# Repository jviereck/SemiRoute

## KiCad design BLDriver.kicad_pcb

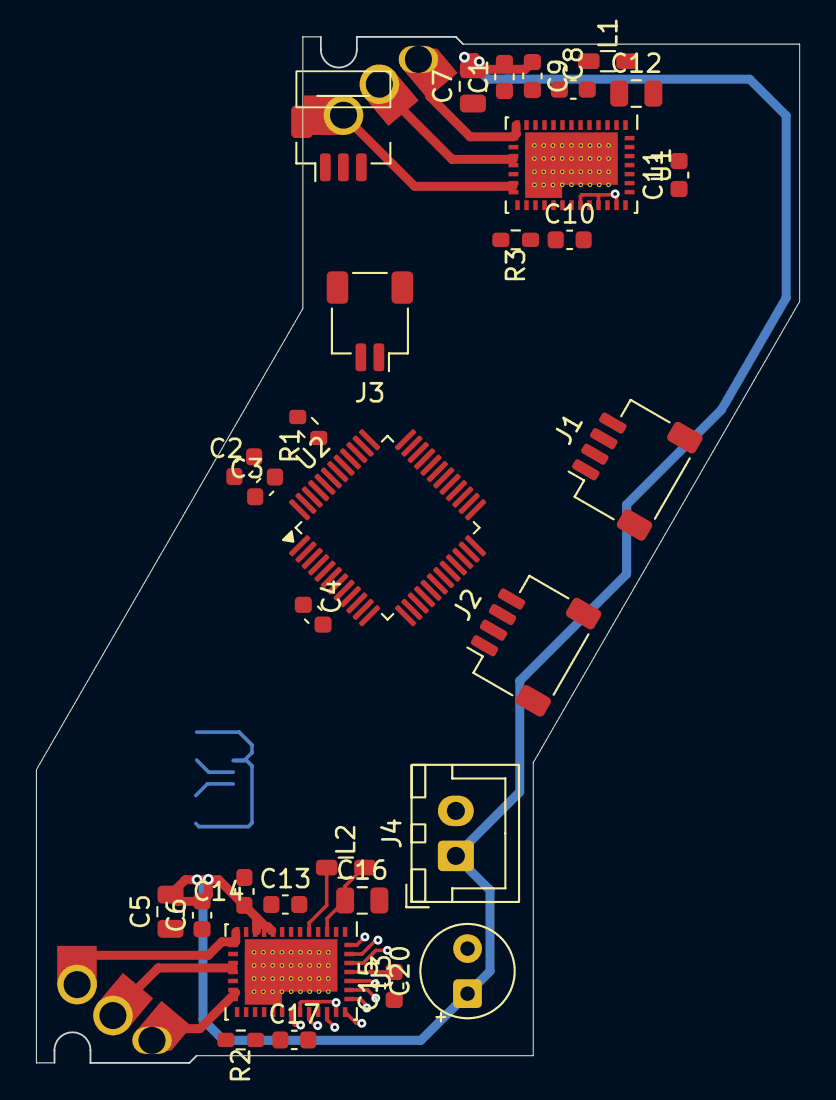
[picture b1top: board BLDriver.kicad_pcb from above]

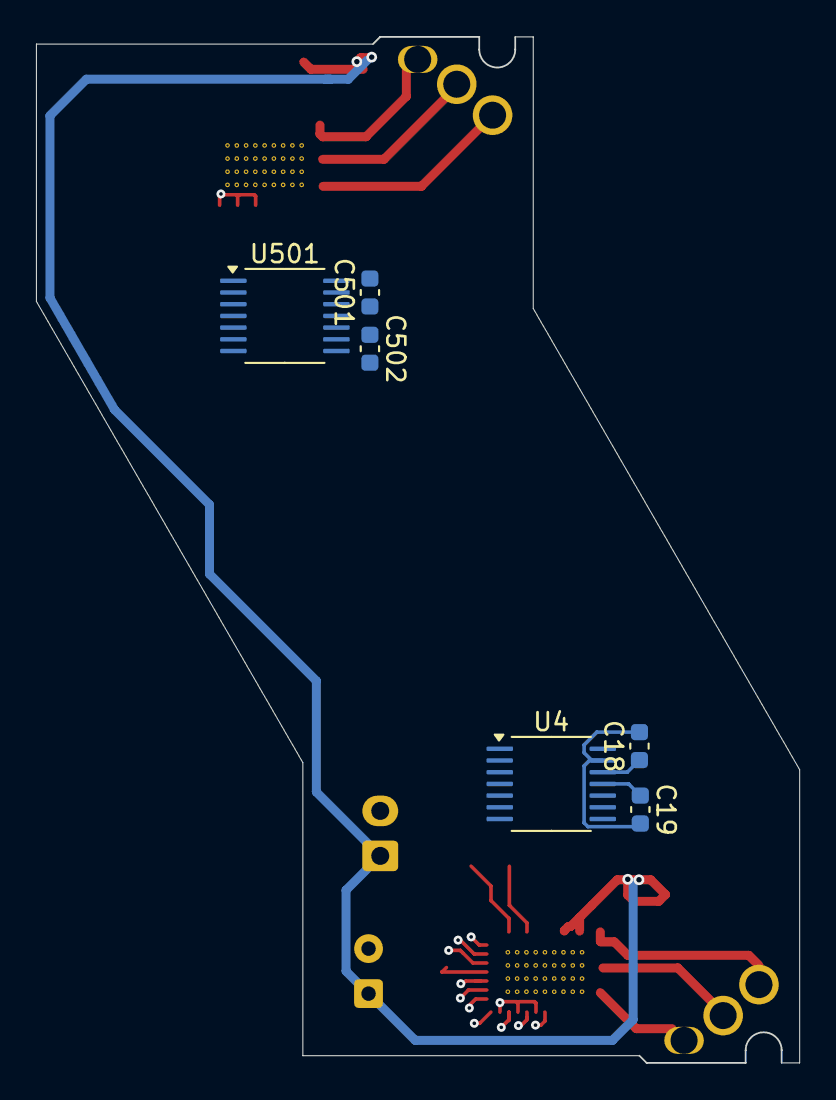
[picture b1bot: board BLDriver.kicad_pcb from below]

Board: 4 copper layers, 42.4 x 57.0 mm, 38 parts (6 on the bottom side), 60 nets.

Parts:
C1, C2, C4, C6, C11, C15: 100nF; C_0603_1608Metric
C3, C9, C10, C14, C17: 1uF; C_0603_1608Metric
C5, C7: 10uF; C_0805_2012Metric
C8, C13: 47nF; C_0603_1608Metric
C12, C16: 22uF; C_0805_2012Metric
C18, C501: 2.2 uF; C_0603_1608Metric
C19, C502: 1 uF; C_0603_1608Metric
C20: 220 uF; CP_Radial_Tantal_D5.0mm_P2.50mm
J1, J2: Conn_01x04_Pin; JST_SH_SM04B-SRSS-TB_1x04-1MP_P1.00mm_Horizontal
J3: Conn_01x02_Pin; JST_SH_SM02B-SRSS-TB_1x02-1MP_P1.00mm_Horizontal
J4: Conn_01x02_Pin; JST_XH_B2B-XH-A_1x02_P2.50mm_Vertical
J5: Conn_01x03_Pin; MotorPogo_A
J6: Conn_01x03_Pin; MotorPogo_B
L1, L2: 47uH; L_0805_2012Metric
R1: 10k; R_0603_1608Metric
R2, R3: 5.1k; R_0603_1608Metric
U1, U3: DRV8316R; QFN-40_EP_5x7_Pitch0.5mm
U2: STM32G071CBT6; LQFP-48_7x7mm_P0.5mm
U4, U501: AS5048A

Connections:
3V3: C2.2, C3.2, C12.1, C18.1, C501.1, L1.2, U1.3 (FB_BK), U2.1 (VDD), U2.9 (VDDA), U2.24 (VDD), U2.48 (VDD), U4.12 (VDD3V), U501.12 (VDD3V)
/DRV8316_setup1/3V3: C16.1, L2.2, U3.3 (FB_BK)
/DRV8316_setup1/INA: U2.29 (PA9/INHB1), U3.27 (INHA)
/DRV8316_setup1/INB: U2.38 (PB5/INHB2), U3.29 (INHB)
/DRV8316_setup1/INC: U2.18 (PB0/INHC2), U3.31 (INHC)
/DRV8316_setup1/IN_ENABLE: U2.32 (PA12/INL_EN2), U3.28 (INLA), U3.30 (INLB), U3.32 (INLC)
/DRV8316_setup1/SOA: U2.20 (PB2/SOA2), U3.40 (SOA)
/DRV8316_setup1/SOB: U2.21 (PB10/SOB2), U3.39 (SOB)
/DRV8316_setup1/SOC: U2.22 (PB11/SOC2), U3.38 (SOC)
/DRV8316_setup1/nFAULT: R2.2, U2.45 (PD2/nFAULT2), U3.22 (~FAULT)
/DRV8316_setup/INA: U1.27 (INHA), U2.28 (PA8/INHA1)
/DRV8316_setup/INB: U1.29 (INHB), U2.37 (PB4/INHA2)
/DRV8316_setup/INC: U1.31 (INHC), U2.30 (PA10/INHC1)
/DRV8316_setup/IN_ENABLE: U1.28 (INLA), U1.30 (INLB), U1.32 (INLC), U2.31 (PA11/INL_EN1)
/DRV8316_setup/SOA: U1.40 (SOA), U2.10 (PA0/SOA1)
/DRV8316_setup/SOB: U1.39 (SOB), U2.11 (PA1/SOB1)
/DRV8316_setup/SOC: U1.38 (SOC), U2.19 (PB1/SOC1)
/DRV8316_setup/nFAULT: R3.2, U1.22 (~FAULT), U2.44 (PD1/nFAULT1)
/STM32G071/I2C1_SCL: J3.2, U2.39 (PB6)
/STM32G071/I2C1_SDA: J3.1, U2.40 (PB7)
/STM32G071/SPI2_MISO: J2.4, U2.26 (PB14/SPI2_MISO)
/STM32G071/SPI2_MOSI: J2.3, U2.27 (PB15/SPI2_MOSI)
/STM32G071/SPI2_NSS: J2.2, U2.23 (PB12/SPI2_NSS)
/STM32G071/SPI2_SCK: J2.1, U2.25 (PB13/SPI2_SCK)
/STM32G071/SWCLK: J1.4, U2.34 (PA14/SWCLK)
/STM32G071/SWDIO: J1.3, U2.33 (PA13/SWDIO)
/STM32G071/UART_RX: J1.2, U2.13 (PA3/UART_RX)
/STM32G071/UART_TX: J1.1, U2.12 (PA2/UART_TX)
CS_DRV1: U1.36 (~SCS), U2.14 (PA4/CS_DRV1)
CS_DRV2: U2.3 (PC14/CS_DRV2), U3.36 (~SCS)
CS_ENC1: U2.4 (PC15/CS_ENC1), U501.2 (CLK)
CS_ENC2: U2.43 (PD0/CS_ENC2), U4.2 (CLK)
DRVOFF: U1.21 (DRVOFF), U2.35 (PA15/DRVOFF), U3.21 (DRVOFF)
GND: C1.1, C2.1, C3.1, C4.2, C5.1, C6.1, C7.1, C10.2, C11.1, C12.2, C15.1, C16.2, C17.2, C18.2, C19.2, C20.2, C501.2, C502.2, J4.2, R1.2, U1.2 (AGND), U1.4 (GND_BK), U1.12 (PGND), U1.15 (PGND), U1.18 (PGND), U1.26 (AGND), U1.41 (EP), U2.8 (VSSA), U2.47 (VSS), U3.2 (AGND), U3.4 (GND_BK), U3.12 (PGND), U3.15 (PGND), U3.18 (PGND), U3.26 (AGND), U3.41 (EP), U4.13 (GND), U501.13 (GND)
unnamed: C10.1, R3.1, U1.25 (AVDD)
unnamed: C9.2, U1.8 (CP)
unnamed: C8.1, U1.7 (CPH)
unnamed: C8.2, U1.6 (CPL)
unnamed: L1.1, U1.5 (SW_BK)
unnamed: C11.2, U1.37 (VREF/ILIM)
unnamed: C4.1, U2.7 (NRST)
unnamed: R1.1, U2.41 (PB8/BOOT0)
unnamed: C17.1, R2.1, U3.25 (AVDD)
unnamed: C14.2, U3.8 (CP)
unnamed: C13.1, U3.7 (CPH)
unnamed: C13.2, U3.6 (CPL)
unnamed: L2.1, U3.5 (SW_BK)
unnamed: C15.2, U3.37 (VREF/ILIM)
unnamed: C19.1, U4.11 (VDD5V)
unnamed: C502.1, U501.11 (VDD5V)
OUTA1: J5.1, U1.13 (OUTA), U1.14 (OUTA)
OUTA2: J6.1, U3.13 (OUTA), U3.14 (OUTA)
OUTB1: J5.2, U1.16 (OUTB), U1.17 (OUTB)
OUTB2: J6.2, U3.16 (OUTB), U3.17 (OUTB)
OUTC1: J5.3, U1.19 (OUTC), U1.20 (OUTC)
OUTC2: J6.3, U3.19 (OUTC), U3.20 (OUTC)
SPI_DEV_CLK: U1.35 (SCLK), U2.15 (PA5/SPI1_SCK), U3.35 (SCLK), U4.1 (CSn), U501.1 (CSn)
SPI_DEV_MISO: U1.33 (SDO), U2.16 (PA6/SPI1_MISO), U3.33 (SDO), U4.3 (MISO), U501.3 (MISO)
SPI_DEV_MOSI: U1.34 (SDI), U2.17 (PA7/SPI1_MOSI), U3.34 (SDI), U4.4 (MOSI), U501.4 (MOSI)
VM: C1.2, C5.2, C6.2, C7.2, C9.1, C14.1, C20.1, J4.1, U1.9 (VM), U1.10 (VM), U1.11 (VM), U3.9 (VM), U3.10 (VM), U3.11 (VM)

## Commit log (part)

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2026-01-31 Adding CLAUDE.md
2026-02-01 Revert "Use CSS transforms for zoom (fixes Firefox lag)"
    This reverts commit 0907741e5b09c142b2f4c3b5d0048c4ea4aee5f7.
2026-02-01 Backspace delete fix
2026-02-01 Remove test file
2026-02-01 Allow individual segment selection and deletion in Trace Mode
2026-02-01 Remove tests output
